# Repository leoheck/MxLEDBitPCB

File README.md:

# infinite possibilities

[Cherry-Mx-Bitboard](https://github.com/ogatatsu/Cherry-Mx-Bitboard) is modified so that SK6812mini is addicted to helix.

Printed circuit board for self-made keyboard, one board corresponds to one switch. 

Using this board, you can create a full-color backlit keyboard with an original layout without designing the board.

For example ...!

[Click here for](https://swan-match.hatenablog.com/entry/2018/09/15/184923) details.

In addition, we disclosed [how](https://swanmatch.github.io/topplate-tips) to [make](https://swanmatch.github.io/topplate-tips) the [top plate](https://swanmatch.github.io/topplate-tips) .

[English](https://translate.google.com/translate?hl=ja&sl=auto&tl=en&u=https%3A%2F%2Fswanmatch.github.io%2FMxLEDBitPCB%2F&sandbox=1)

## Infinite possibilities series

### ProMicro House

A ProMicro pin that can be taken out, plus an OLED, reset switch, TRRS for split keyboard, and M2 screw holes for mounting.
 TRRS pin assignment is Helix compatible.

### Nexus

Unless the original 25 keys are disconnected, Col and Row and vertical VCC and GND do not require wiring.

Of course, it can be used even if separated.

### Altana

Pre-wired version like Nexus, and switchable version with Kailh socket.

## Material example (supplier)

- Arbitrarily cut plate
    - 2mm acrylic board (Yusha studio)
         It is good to have an adhesive such as 3mm acrylic timber and acrylic sundae. (Home center)
    - 3D case (DMM.make)
    - 5mm cardboard (such as picked up from there)
- Switching diode 1N4148 (TALPKeyboard)
- SK6812mini (Yusha studio)
- Urethane enameled wire (recommended is 0.35 to 0.45mm. It is also available at home improvement stores. It is possible to use vinyl wire, but it will melt or be quite difficult)
- TRRS jack, RESET button (Mr. Akizuki Denshi)
- OLED (optional, Yusha Kobo)
- Promicro (Yusha Kobo, TALPkeyboard)
- Various spacers and screws (Hirosugi Keiki, Wilco, etc.)
- Key switches, keycaps (Yusha Kobo, TalpKeyboard, etc. according to your preference)
- USB cable, TRS (3.5mm3 pole) cable

In addition, tools such as a temperature control soldering iron, tester, and tweezers are required.

## Pin assignment

The pinouts of the infinite possibilities are:

- C: Horizontal line (Col)
- R: Vertical line (Row)
- DI: LED control signal input (DataIn)
- DO: LED control signal output (DataOUT)
- -: Ground (for LED)
- +: VCC (5V for LED)

## Assembly procedure

1. Solder SK6812mini.
     Solder at about 220 ° C with a temperature-adjustable soldering iron.
     It will break if it is stuck.
     Use low-temperature solder with a melting point of 200 ° C or less.
2. Solder the diode.
3. Place the switch on the top plate and solder the switch legs with infinite possibilities on the back.
     (Altana is a socket.) If you use a 2mm acrylic board at this time, it is good to attach a 3mm acrylic material to the switch side on the back of the plate with acrylic adhesive to prevent the switch from coming off.
4. Wire the horizontal line (Col) and the vertical line (Row) according to the key matrix of the keyboard you want to build.
5. Connect all "-" and "+".
6. Wire the beads from DI to DO in the order you want the LEDs to shine. First DO → Second DI → Second DO → Third DI ...
7. Solder TRRSJACK and RESET switch.
8. Solder the OLED socket.
9. Wire Col and Row, LED (DO), GND, VCC from the hole next to any pin for each of the infinite possibilities.
10. Solder the Promicro to the socket.
     (Although you can use a con through, but it is cheaper to replace the whole socket if it breaks.)
11. Create and write firmware to your liking and complete.
     The firmware is very simple using [QMK_Firmware](https://github.com/qmk/qmk_firmware) .
     Reference: [Three types of means to prepare firmware for your own keyboard](https://skyhigh-works.hatenablog.com/entry/2018/10/09/120909)

## Wiring example

For example, if you have a 3 * 3 grid array, the wiring will be as follows.
 (If you do not disconnect the Nexus Altana, the wiring of Col, Row, vertical VCC and GND between the boards is unnecessary.)
 Urethane enameled wire (UEW) is quite difficult to peel off the film, so the wiring between adjacent boards where the possibility of short-circuiting is small may be a cut-off diode foot.
 The LED is wired spirally from the upper right.

### Notes

- Nexus Altana, which has been in circulation since April 2019, has already been wired with Col, Row and vertical power lines (VCC, GND).
- Altana is a version that allows you to replace the switch using a Kailh socket.
- If you don't need to illuminate the LED by all means, just wire Col and Row and it will work as a keyboard.
- In the case of sandwich-mounted keyboards, which are widely used in Japan, the top plate and the bottom plate are arranged with spacers, but in the case of infinite possibilities, there is no gap between the keys. Provide a screw hole on the outside of the key.
- If you solder the Promicro first to the “home,” when wiring to the infinite possibility, the solder may leak out of the hole and short-circuit parts of the Promicro body.
     Promicro should be soldered last.

## At the end

If you use this board to build a keyboard, please let us [know](https://twitter.com/swan_match) at [@swan_match](https://twitter.com/swan_match) .

I support your EndGame! !

## License

https://creativecommons.org/licenses/by/4.0/

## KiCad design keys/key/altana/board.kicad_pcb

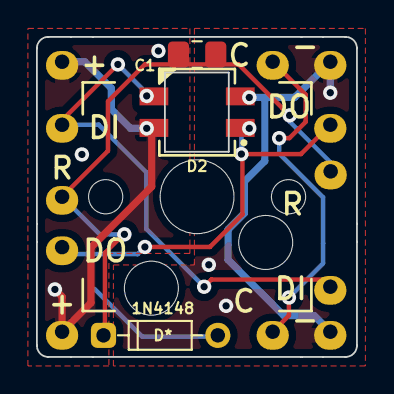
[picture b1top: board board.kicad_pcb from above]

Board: 2 copper layers, 17.8 x 17.8 mm, 16 parts (0 on the bottom side), 7 nets.

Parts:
C1: C_Small; C_0805_2012Metric_Pad1.18x1.45mm_HandSolder
D1: 1N4148; diode
D2: SK6812MINI
J1, J7: (+); wirepad
J2, J8: (-); wirepad
J3, J9: C; wirepad
J4, J10: R; wirepad
J5, J11: DI; wirepad
J6, J12: DO; wirepad
SW1: SW_Push; Switch_MX_Hotswap

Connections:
/key/COL_N: J3.1, J9.1, SW1.1
/key/LED_DI: D2.3, J5.1, J11.1
/key/LED_DO: D2.1, J6.1, J12.1
/key/ROW_N: D1.1, J4.1, J10.1
GND: C1.2, D2.2, J2.1, J8.1
unnamed: D1.2, SW1.2
VCC: C1.1, D2.4, J1.1, J7.1

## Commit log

2020-09-23 Update READMEs
2020-09-27 Move projects improving organization
2020-09-27 Update Library
2020-09-27 Update organization
2020-09-27 Restore original panel
2020-09-28 Add original key design with no changes
2020-09-28 Remove extra files
2020-09-28 Use a standard name
2020-09-28 User a common name for the footprint library
2020-09-29 Move library files to a folder
2020-09-29 Update project using kicad symbols whenever is possible and also update footprints to use project's library
2020-09-29 Adding extra footprints and 3d models
2020-09-29 Remove wrong path
2020-09-29 Improve projects library
2020-09-29 Add bck to .gitignore
2020-09-29 Update symbols cache lib
2020-09-29 Update board by using components from the project library
2020-09-29 Add initial 3d model of the board
2020-09-29 Update project's footprints
2020-09-29 Add decoupling capacitor for the LED board
2020-09-29 Update symbols cache
2020-09-29 Update footprints cache
2020-09-29 Add extra capacitor and make it more flexible for panels
2020-09-29 Add initial README for this project
2020-09-29 Update connections
2020-09-29 Update panel bridges
